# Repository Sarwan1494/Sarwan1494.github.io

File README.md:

# Portfolio

Plain HTML / CSS / JS, no build step, no framework, no dependencies except
KiCanvas (loaded from `kicanvas.org` via `<script type="module">` on the
project pages) for the in-browser KiCad viewer.

```
portfolio/
├── index.html                          # home page (about, project grid, contact)
├── projects/
│   ├── so101-robot-arm.html            # ROS 2 / MoveIt 2 project (webm video)
│   ├── mars-rover.html                 # Ackermann rover, Arduino + ROS 2 (webm video, inline SVG diagrams)
│   ├── vacuum-robot-simscape.html      # master's thesis, Simscape vacuum robot model (3 webm videos)
│   ├── nema17-stepper-driver.html      # project detail + KiCanvas embed
│   ├── cylinder-assembly.html          # CAD animation (webm video)
│   ├── delta-robot.html                # CAD animation (webm video)
│   ├── two-wheel-robot.html            # wiring schematic (png)
│   └── inverted-pendulum.html          # CAD animation (webm video)
├── assets/
│   ├── css/style.css
│   ├── js/main.js                      # theme toggle + viewer tab logic
│   ├── img/                            # renders / screenshots / video posters
│   ├── video/                          # project animations (.webm)
│   └── kicad/                          # .kicad_sch / .kicad_pcb / .kicad_pro served as static files
└── downloads/                          # schematic PDF, gerbers, interactive BOM, STEP model
```

## Running locally

KiCanvas fetches the `.kicad_sch` / `.kicad_pcb` files over `fetch()`, which
browsers block on `file://`. Serve the folder over HTTP instead:

```bash
cd portfolio
python3 -m http.server 8000
# open http://localhost:8000
```

## Adding a new project

1. Duplicate `projects/nema17-stepper-driver.html` as a starting point.
2. Drop images in `assets/img/`, KiCad source in `assets/kicad/`,
   downloadables in `downloads/`.
3. Add a card to the `.projects-grid` in `index.html`.

## Before publishing

- Replace the LinkedIn / GitHub placeholder links in `index.html` (`#contact`).
- `downloads/nema17-3d-model.step` is ~16 MB. Most static hosts (GitHub
  Pages, Netlify, Vercel) are fine with that per file, but if you're using
  git, consider Git LFS or dropping the STEP download if repo size matters.
- Everything else is small and framework-free, so it deploys to any static
  host (GitHub Pages, Netlify, Vercel, S3, ...) with no build step.

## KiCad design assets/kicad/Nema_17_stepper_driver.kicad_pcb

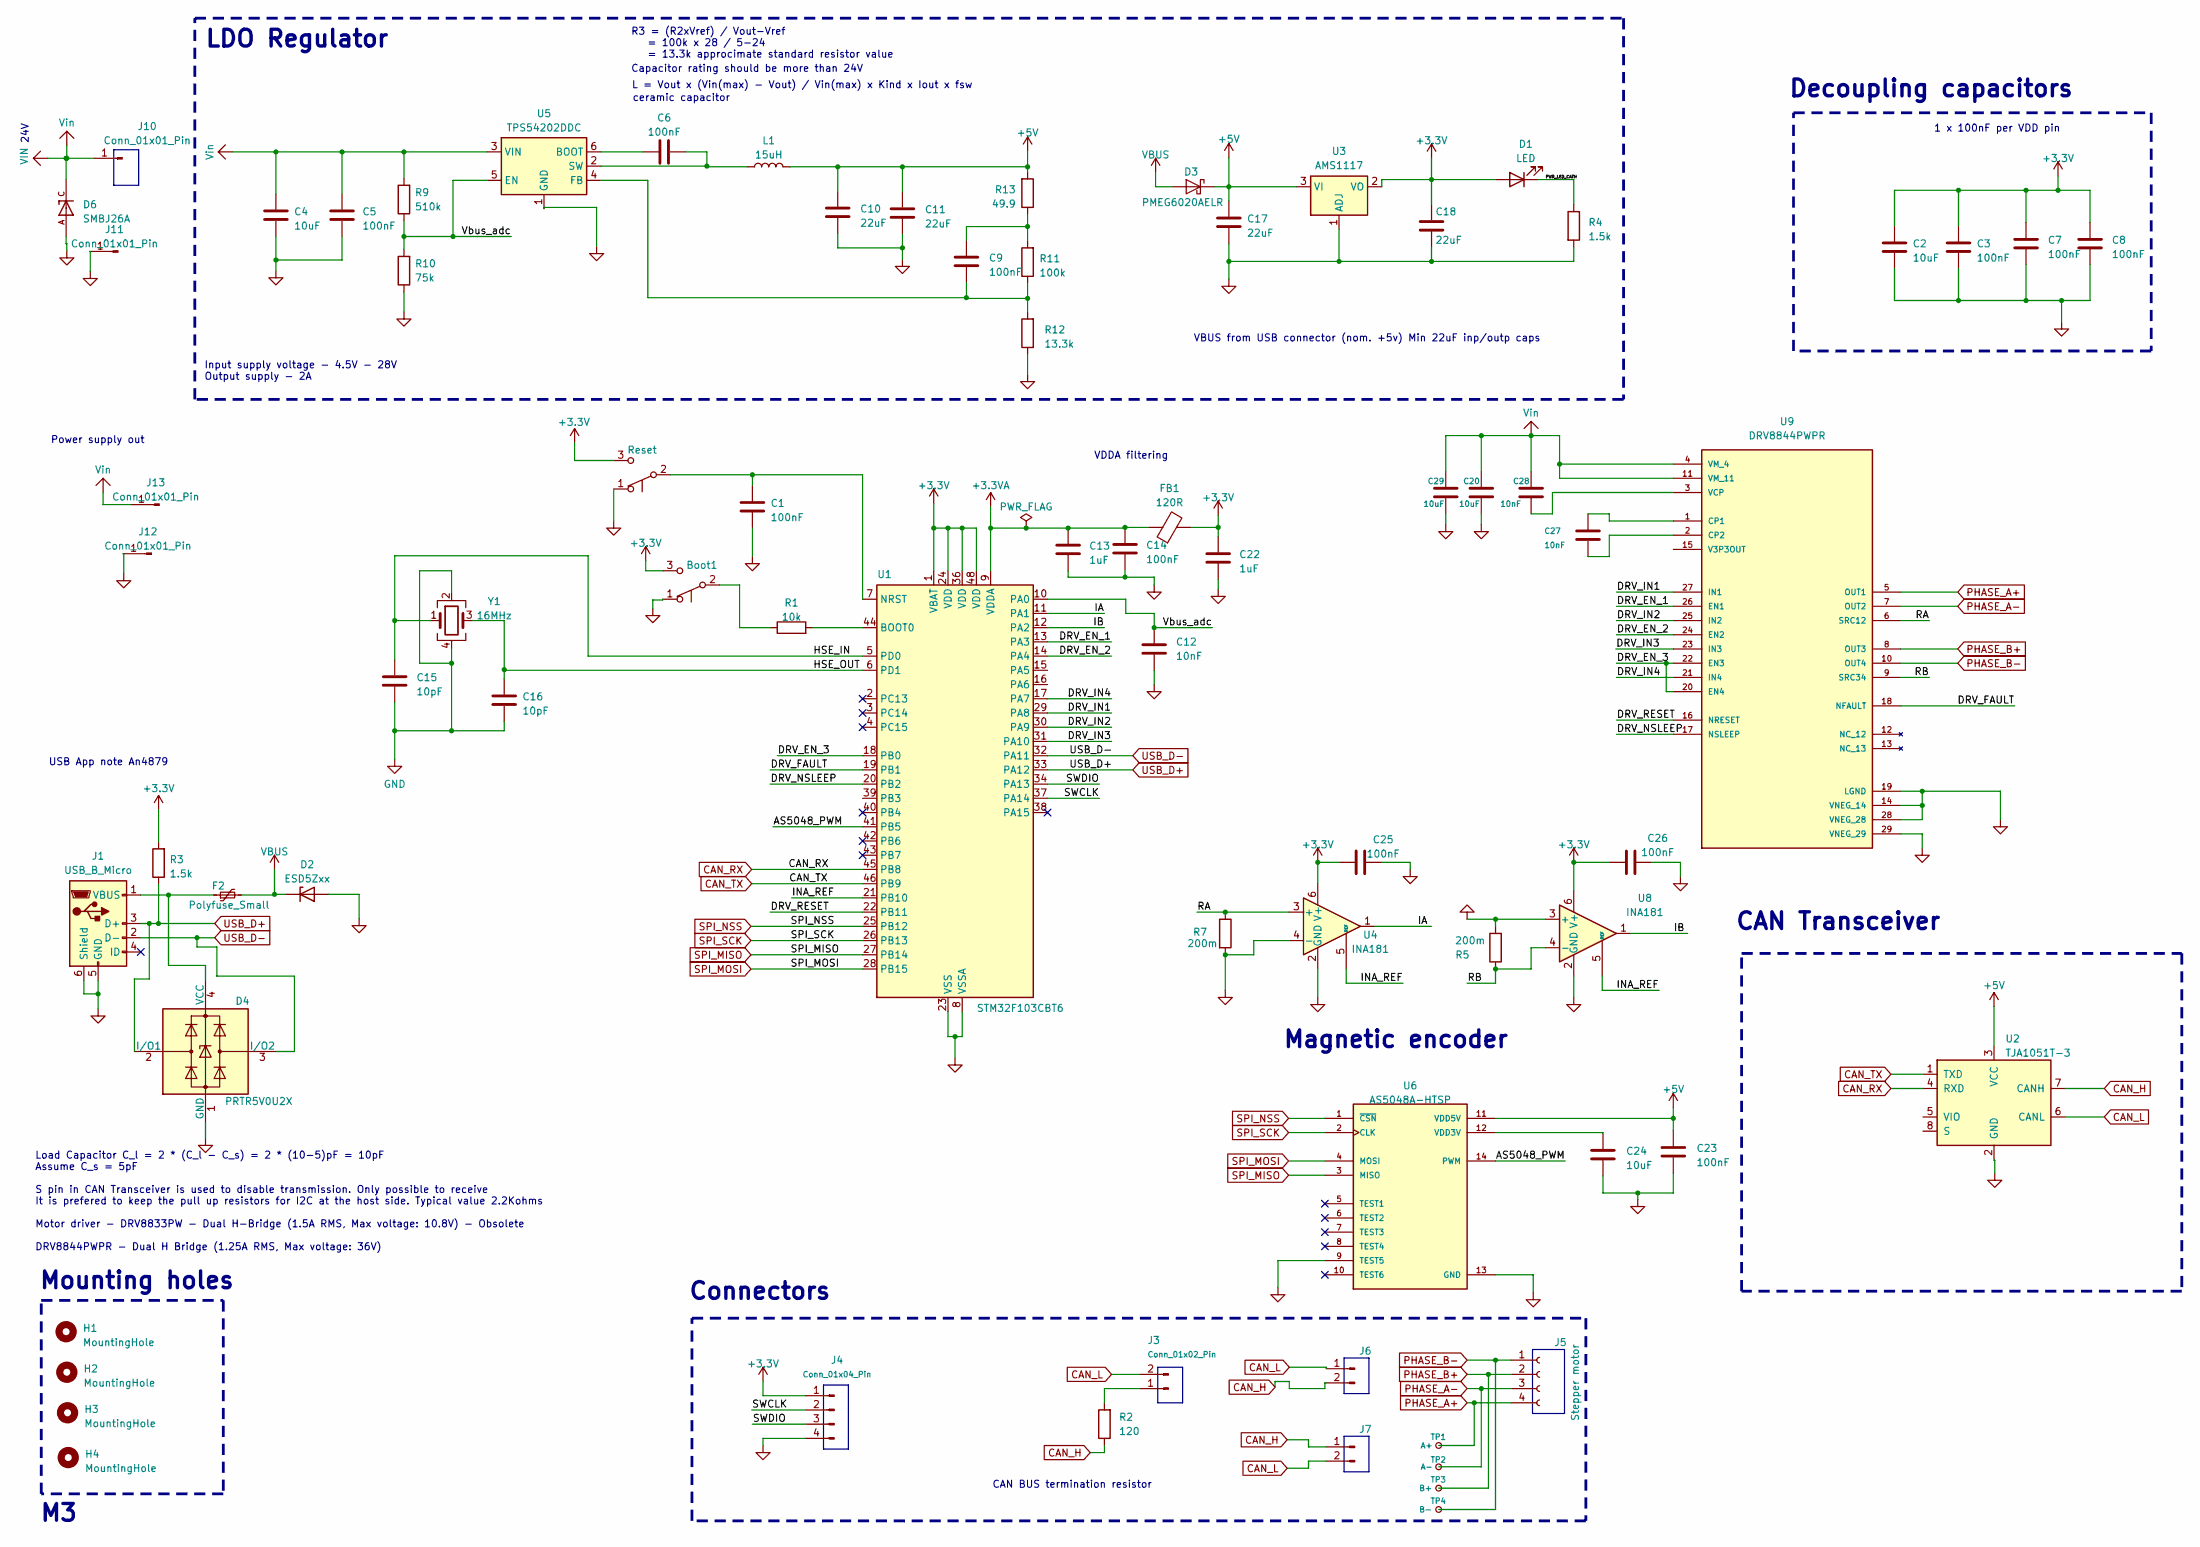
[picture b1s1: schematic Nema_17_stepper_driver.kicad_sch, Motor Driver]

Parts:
Boot1: Boot; SW_SPST_B3U-1100P; LCSC C2680611
C1, C3, C5, C6, C7, C8, C9, C14, C23, C25, C26: 100nF; C_0402_1005Metric; LCSC C152814
C2, C4, C20, C24, C29: 10uF; C_0805_2012Metric; LCSC C2932476
C10, C11, C17, C18: 22uF; C_0805_2012Metric; LCSC C2179409
C12, C27, C28: 10nF; C_0402_1005Metric; LCSC C15195
C13, C22: 1uF; C_0402_1005Metric; LCSC C1518208
C15, C16: 10pF; C_0402_1005Metric; LCSC C106199
D1: LED; LED_0603_1608Metric; LCSC C598384
D2: ESD5Zxx; D_SOD-523; LCSC C2890110
D3: PMEG6020AELR; Nexperia_CFP3_SOD-123W; LCSC C52754489
D4: PRTR5V0U2X; SOT-143; LCSC C5180302
D6: SMBJ26A; DIOM4336X265N; PARTREV F2102; LCSC C908802
F2: Polyfuse_Small; FUSM4632X85; LCSC C3761417
FB1: 120R; L_0603_1608Metric; LCSC C127301
H1, H2, H3, H4: MountingHole; MountingHole_3.2mm_M3_ISO7380_Pad
J1: USB_B_Micro; USB_Micro-B_Wuerth_629105150521; LCSC C40943
J3: Conn_01x02_Pin; SolderJumper-2_P1.3mm_Open_TrianglePad1.0x1.5mm; LCSC C53055365
J4: Conn_01x04_Pin; PinHeader_1x04_P2.54mm_Vertical
J5: Stepper motor; Molex_PicoBlade_53048-0410_1x04_P1.25mm_Horizontal; LCSC C588275
J6, J7: Conn_01x02_Pin; Molex_PicoBlade_53048-0210_1x02_P1.25mm_Horizontal; LCSC C53055365
J10, J11, J12, J13: Conn_01x01_Pin; TestPoint_Keystone_5019_Minature
L1: 15uH; L_0603_1608Metric; LCSC C53145222
R1: 10k; R_0603_1608Metric; LCSC C2906982
R2: 120; R_0603_1608Metric; LCSC C2907096
R3: 1.5k; R_0603_1608Metric; LCSC C2930050
R4: 1.5k; R_0402_1005Metric; LCSC C2930050
R5, R7: 200m; R_1206_3216Metric; LCSC C46444578
R9: 510k; R_0603_1608Metric; LCSC C2907047
R10: 75k; R_0603_1608Metric; LCSC C2907072
R11: 100k; R_0603_1608Metric; LCSC C2906980
R12: 13.3k; R_0603_1608Metric; LCSC C2933140
R13: 49.9; R_0603_1608Metric; LCSC C2930110
Reset1: Reset; SW_SPST_B3U-1100P; LCSC C2680611
TP1: A+; TestPoint_Pad_D1.0mm
TP2: A-; TestPoint_Pad_D1.0mm
TP3: B+; TestPoint_Pad_D1.0mm
TP4: B-; TestPoint_Pad_D1.0mm
U1: STM32F103CBT6; LQFP-48_7x7mm_P0.5mm; LCSC C8304
U2: TJA1051T-3; SOIC-8_3.9x4.9mm_P1.27mm; LCSC C177807
U3: AMS1117; SOT-223-3_TabPin2; LCSC C6186
U4, U8: INA181; SOT-23-6; LCSC C2058943
U5: TPS54202DDC; SOT-23-6; LCSC C191884
U6: AS5048A-HTSP; SOP65P640X120-14N; LCSC C2655181
U9: DRV8844PWPR; IC_DRV8844PWPR; PARTREV D; LCSC C177807
Y1: 16MHz; Crystal_SMD_3225-4Pin_3.2x2.5mm; LCSC C13738

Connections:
+3.3V: Boot1.3 (C), C2.1, C3.1, C7.1, C8.1, C18.1, C22.1, C25.1, C26.1, D1.2 (A), FB1.2, J4.1, R3.2, Reset1.3 (C), U1.1 (VBAT), U1.24 (VDD), U1.36 (VDD), U1.48 (VDD), U3.2 (VO), U4.6 (V+), U8.6 (V+)
+3.3VA: C13.1, C14.1, FB1.1, U1.9 (VDDA)
+5V: C10.2, C11.2, C17.1, C23.1, D3.1 (K), L1.1, R13.2, U2.3 (VCC), U3.3 (VI), U6.11 (VDD5V)
/AS5048_PWM: U1.41 (PB5), U6.14 (PWM)
/DRV_EN_1: U1.13 (PA3), U9.26 (EN1)
/DRV_EN_2: U1.14 (PA4), U9.24 (EN2)
/DRV_EN_3: U1.18 (PB0), U9.20 (EN4), U9.22 (EN3)
/DRV_FAULT: U1.19 (PB1), U9.18 (NFAULT)
/DRV_IN1: U1.29 (PA8), U9.27 (IN1)
/DRV_IN2: U1.30 (PA9), U9.25 (IN2)
/DRV_IN3: U1.31 (PA10), U9.23 (IN3)
/DRV_IN4: U1.17 (PA7), U9.21 (IN4)
/DRV_NSLEEP: U1.20 (PB2), U9.17 (NSLEEP)
/DRV_RESET: U1.22 (PB11), U9.16 (NRESET)
/HSE_IN: C15.1, U1.5 (PD0), Y1.1
/HSE_OUT: C16.1, U1.6 (PD1), Y1.3
/IA: U1.11 (PA1), U4.1
/IB: U1.12 (PA2), U8.1
/INA_REF: U1.21 (PB10), U4.5 (REF), U8.5 (REF)
/PWR_LED_CATH: D1.1 (K), R4.1
/RA: R7.1, U4.3 (+), U9.6 (SRC12)
/RB: R5.1, U8.4 (-), U9.9 (SRC34)
/SWCLK: J4.2, U1.37 (PA14)
/SWDIO: J4.3, U1.34 (PA13)
/Vbus_adc: C12.1, R9.1, R10.2, U1.10 (PA0), U5.5 (EN)
CAN_H: J6.2, J7.1, R2.1, U2.7 (CANH)
CAN_L: J3.2, J6.1, J7.2, U2.6 (CANL)
CAN_RX: U1.45 (PB8), U2.4 (RXD)
CAN_TX: U1.46 (PB9), U2.1 (TXD)
GND: Boot1.1 (A), C1.2, C2.2, C3.2, C4.2, C5.2, C7.2, C8.2, C10.1, C11.1, C12.2, C13.2, C14.2, C15.2, C16.2, C17.2, C18.2, C20.2, C22.2, C23.2, C24.2, C25.2, C26.2, C29.2, D2.2 (A), D4.1 (GND), D6.A, J1.5 (GND), J1.6 (Shield), J4.4, J11.1, J12.1, R4.2, R5.2, R7.2, R10.1, R12.1, Reset1.1 (A), U1.8 (VSSA), U1.23 (VSS), U1.35 (VSS), U1.47 (VSS), U2.2 (GND), U3.1 (ADJ), U4.2 (GND), U4.4 (-), U5.1 (GND), U6.9 (TEST5), U6.13 (GND), U8.2 (GND), U8.3 (+), U9.14 (VNEG_14), U9.19 (LGND), U9.28 (VNEG_28), U9.29 (VNEG_29), Y1.2, Y1.4
unnamed: Boot1.2 (B), R1.1
unnamed: C9.2, R11.2, R13.1
unnamed: D4.4 (VCC), F2.1, J1.1 (VBUS)
unnamed: J3.1, R2.2
unnamed: C1.1, Reset1.2 (B), U1.7 (NRST)
unnamed: R1.2, U1.44 (BOOT0)
unnamed: C6.1, U5.6 (BOOT)
unnamed: C9.1, R11.1, R12.2, U5.4 (FB)
unnamed: C6.2, L1.2, U5.2 (SW)
unnamed: C24.1, U6.12 (VDD3V)
unnamed: C27.2, U9.1 (CP1)
unnamed: C27.1, U9.2 (CP2)
unnamed: C28.1, U9.3 (VCP)
PHASE_A+: J5.4, TP1.1, U9.5 (OUT1)
PHASE_A-: J5.3, TP2.1, U9.7 (OUT2)
PHASE_B+: J5.2, TP3.1, U9.8 (OUT3)
PHASE_B-: J5.1, TP4.1, U9.10 (OUT4)
SPI_MISO: U1.27 (PB14), U6.3 (MISO)
SPI_MOSI: U1.28 (PB15), U6.4 (MOSI)
SPI_NSS: U1.25 (PB12), U6.1 (~CSN)
SPI_SCK: U1.26 (PB13), U6.2 (CLK)
USB_D+: D4.2 (I/O1), J1.3 (D+), R3.1, U1.33 (PA12)
USB_D-: D4.3 (I/O2), J1.2 (D-), U1.32 (PA11)
VBUS: D2.1 (K), D3.2 (A), F2.2
Vin: C4.1, C5.1, C20.1, C28.2, C29.1, D6.C, J10.1, J13.1, R9.2, U5.3 (VIN), U9.4 (VM_4), U9.11 (VM_11)

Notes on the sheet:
Capacitor rating should be more than 24V
ceramic capacitor
Magnetic encoder
USB App note An4879
L = Vout x (Vin(max) - Vout) / Vin(max) x Kind x Iout x fsw
VBUS from USB connector (nom. +5v) Min 22uF inp/outp caps
24V
LDO Regulator
Mounting holes
CAN Transceiver
Input supply voltage - 4.5V - 28V Output supply - 2A
VDDA filtering
CAN BUS termination resistor
Load Capacitor C_l = 2 * (C_l - C_s) = 2 * (10-5)pF = 10pF Assume C_s = 5pF S pin in CAN Transceiver is used to disable transmission. Only possible to receive It is prefered to keep the pull up resistors for I2C at the host side. Typical value 2.2Kohms Motor driver - DRV8833PW - Dual H-Bridge (1.5A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
R3 = (R2xVref) / Vout-Vref = 100k x 28 / 5-24 = 13.3k approcimate standard resistor value
Power supply out
Decoupling capacitors
Connectors
1 x 100nF per VDD pin

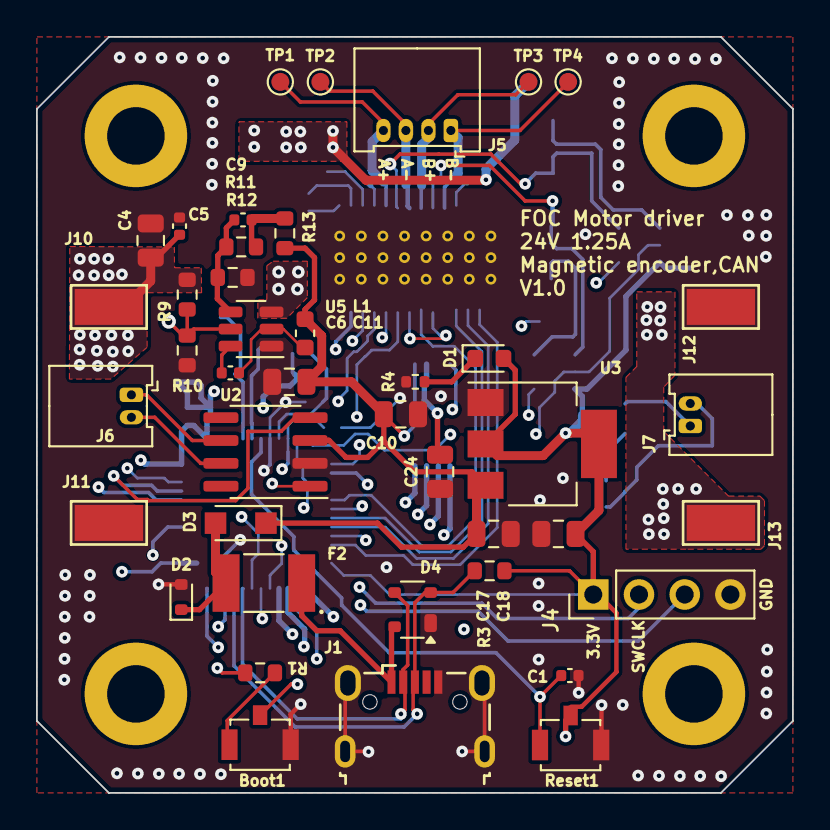
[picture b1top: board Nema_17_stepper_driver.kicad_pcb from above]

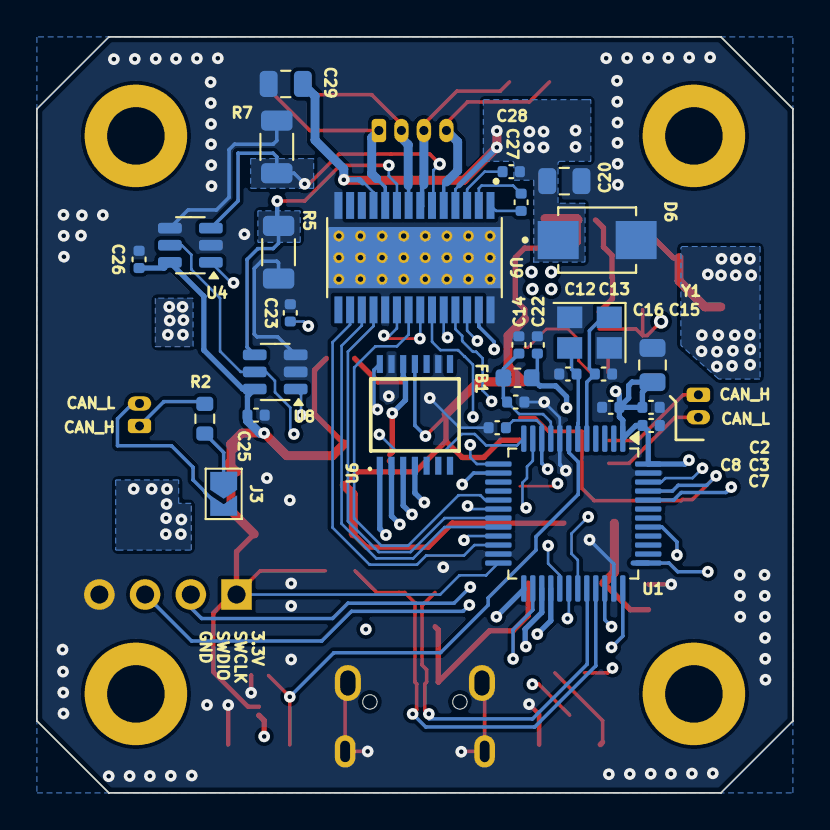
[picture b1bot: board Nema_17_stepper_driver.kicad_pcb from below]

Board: 4 copper layers, 42.0 x 42.0 mm, 75 parts (29 on the bottom side), 55 nets.
